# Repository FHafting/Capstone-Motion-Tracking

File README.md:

# Capstone Motion Tracking
 Repository for MSE4499 capstone project

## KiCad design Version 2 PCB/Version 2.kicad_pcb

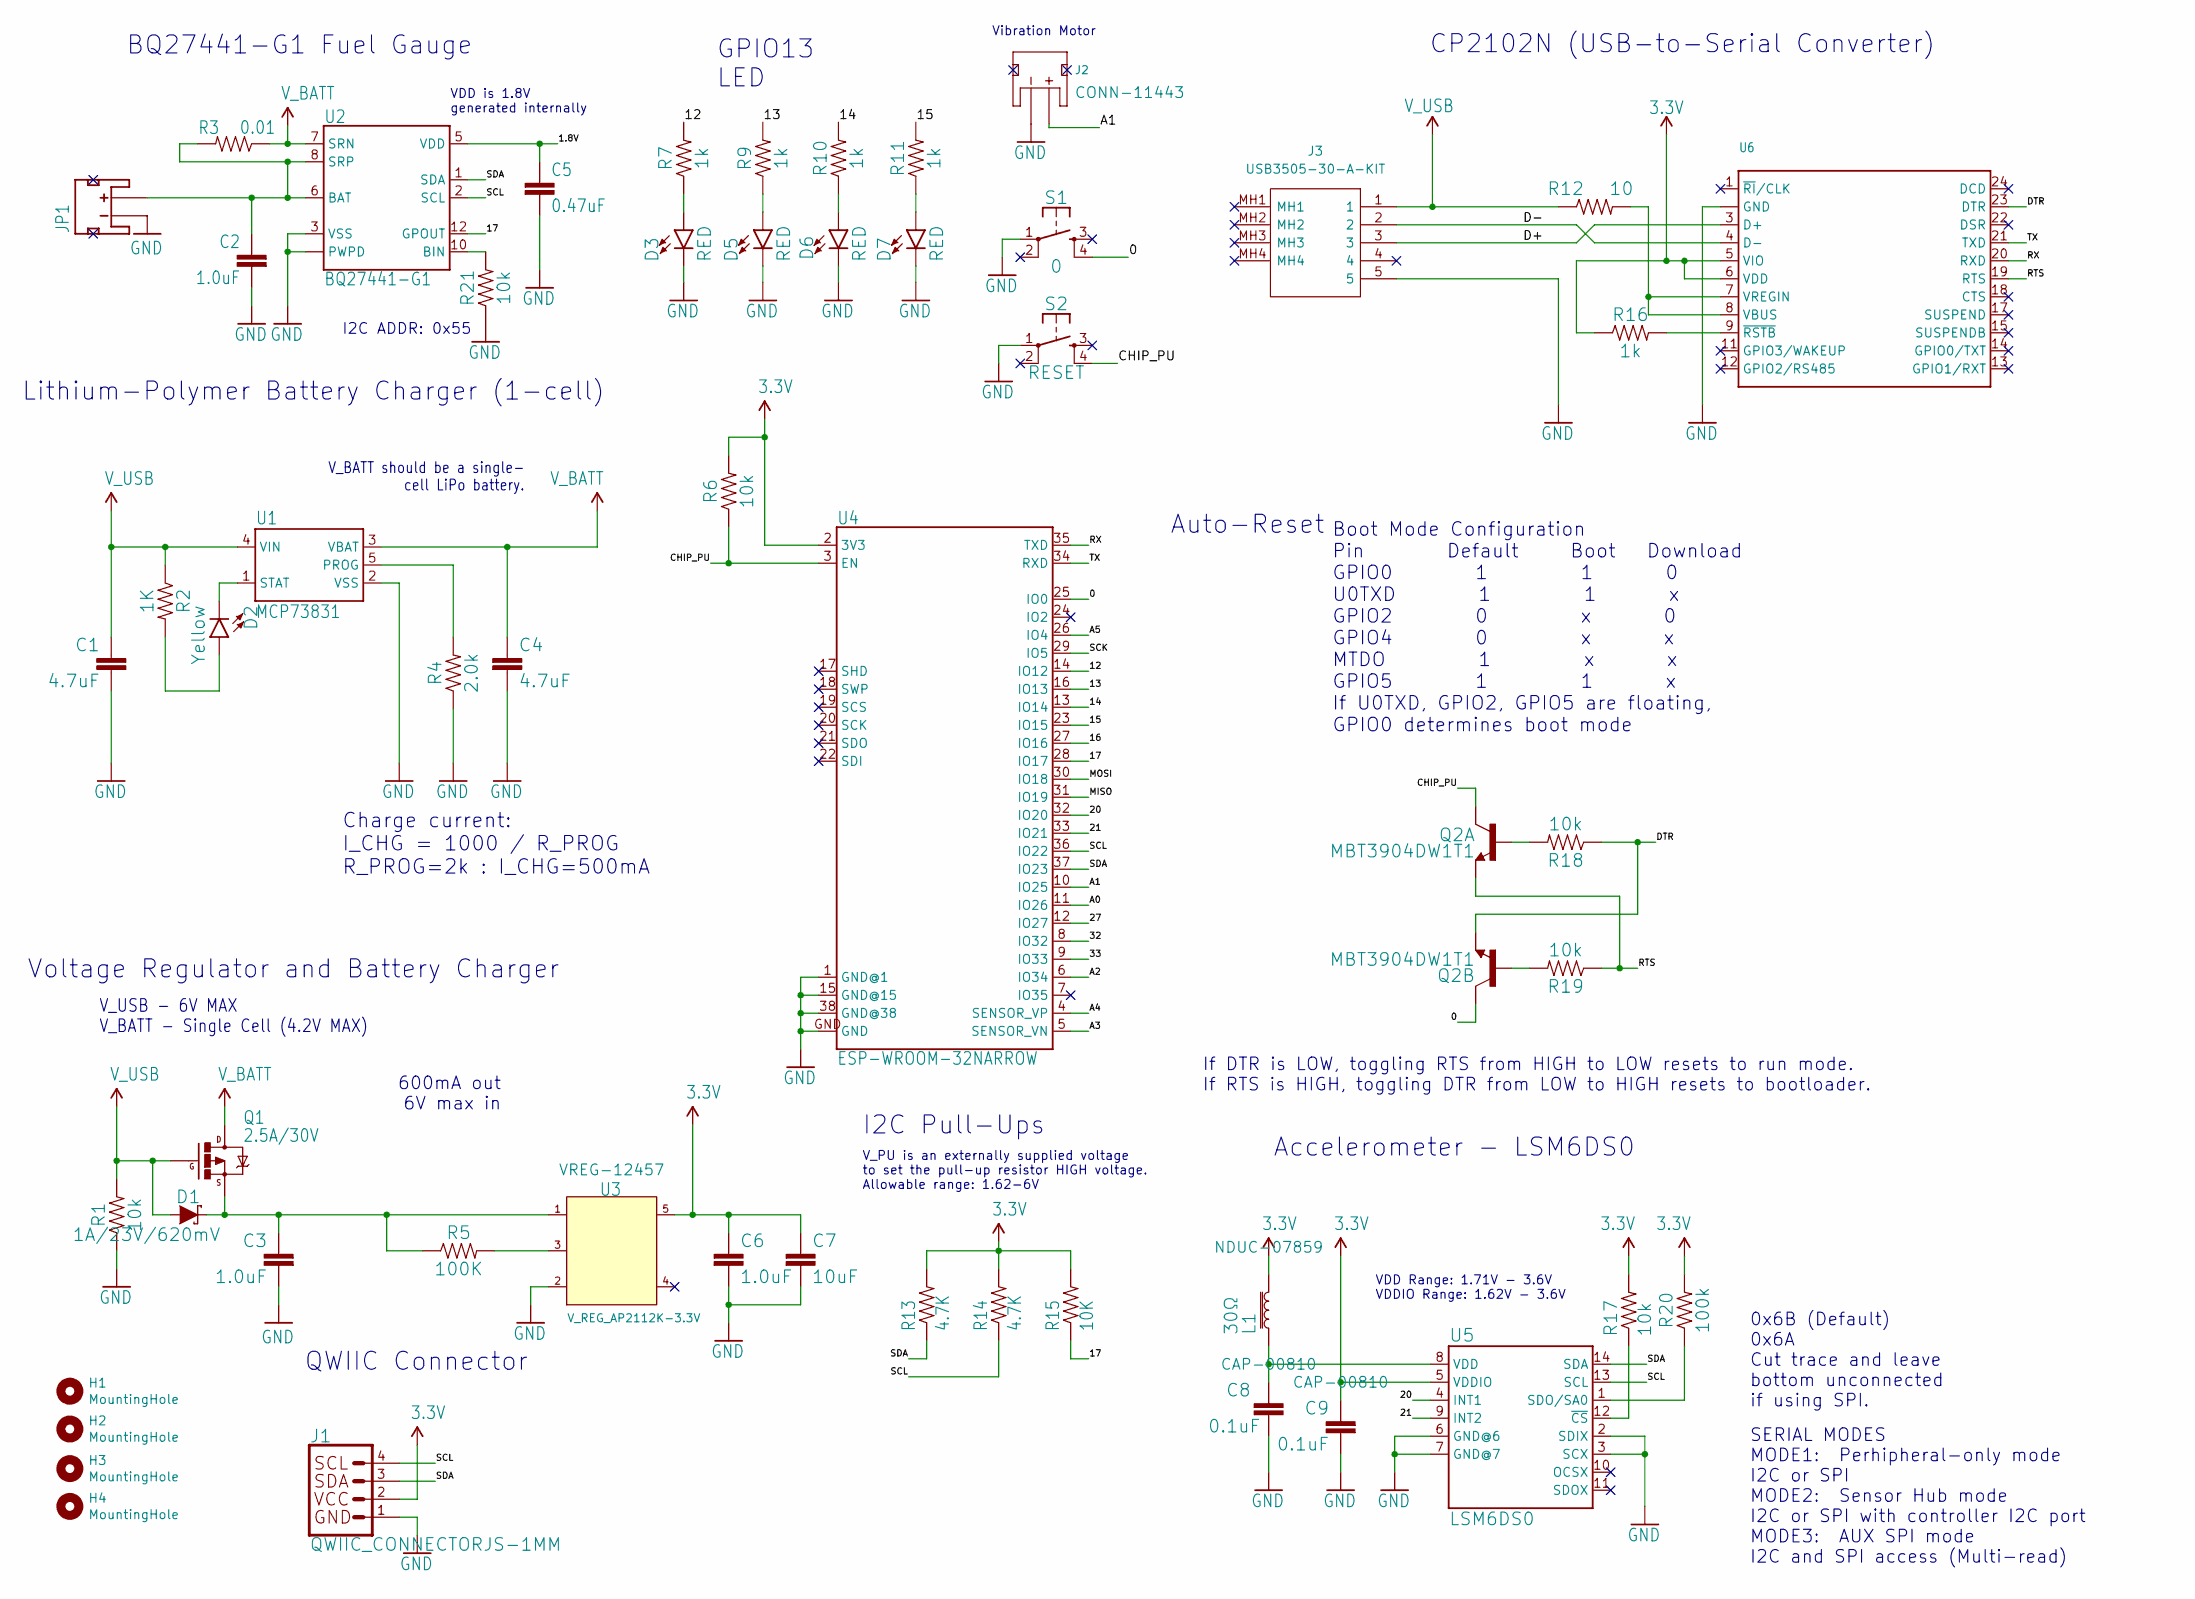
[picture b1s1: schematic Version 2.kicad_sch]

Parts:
C1, C4: 4.7uF; C_0603_1608Metric
C2, C3: 1.0uF; C_0603_1608Metric
C5: C_0603_1608Metric
C6: 1.0uF; 0402
C7: 10uF; C_0603_1608Metric
C8, C9: 0.1uF; C_0603_1608Metric
D1: 1A/23V/620mV; D_SOD-323
D2: Yellow; LED-0603
D3, D5, D6, D7: RED; LED-0603
H1, H2, H3, H4: MountingHole; MountingHole_2mm
J1: QWIIC_CONNECTORJS-1MM; 1X04_1MM_RA
J2: JST_2MM_MALE; JST-2-SMD
J3: USB3505-30-A-KIT; USB350530AKIT; Manufacturer_Part_Number USB3505-30-A-KIT; Mouser Part Number 640-USB3505-30-A-KIT
JP1: JST_2MM_MALE; JST-2-SMD
L1: 30Ω; 0603
Q1: 2.5A/30V; SOT23-3
Q2: MBT3904DW1T1; SC70-6
R1, R6, R17, R18, R19, R21: 10k; 0603
R2: 1K; 0603
R3: 1206
R4: 2.0k; 0603
R5: 100K; 0402
R7, R9, R10, R11, R16: 1k; 0603
R12: 10; 0603
R13, R14: 4.7K; 0603
R15: 10K; 0603
R20: 100k; 0603
S1: 0; TACTILE_SWITCH_SMD_4.6X2.8MM
S2: RESET; TACTILE_SWITCH_SMD_4.6X2.8MM
U1: MCP73831; SOT23-5
U2: PDSO-N12
U3: V_REG_AP2112K-3.3V; SOT23-5
U4: ESP32-WROOM-32
U5: LSM6DS0; LGA-14_3x2.5mm_P0.5mm_LayoutBorder3x4y
U6: (no value)

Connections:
3.3V: C6.1, C7.1, C9.1, J1.2, L1.1, R6.2, R13.2, R14.2, R15.2, R16.1, R17.2, R20.2, U3.5 (OUT), U4.2 (3V3), U5.5 (VDDIO), U6.5 (VIO), U6.6 (VDD)
/0: Q2.6 (C), S1.4, U4.25 (IO0)
/1.8V: C5.1, U2.5 (VDD)
/12: R7.2, U4.14 (IO12)
/13: R9.2, U4.16 (IO13)
/14: R10.2, U4.13 (IO14)
/15: R11.2, U4.23 (IO15)
/16: U4.27 (IO16)
/17: R15.1, U2.12 (GPOUT), U4.28 (IO17)
/20: U4.32 (IO20), U5.4 (INT1)
/21: U4.33 (IO21), U5.9 (INT2)
/27: U4.12 (IO27)
/32: U4.8 (IO32)
/33: U4.9 (IO33)
/A0: U4.11 (IO26)
/A1: J2.2 (+), U4.10 (IO25)
/A2: U4.6 (IO34)
/A3: U4.5 (SENSOR_VN)
/A4: U4.4 (SENSOR_VP)
/A5: U4.26 (IO4)
/CHIP_PU: Q2.3 (C), R6.1, S2.4, U4.3 (EN)
/D+: J3.3, U6.3 (D+)
/D-: J3.2, U6.4 (D-)
/DTR: Q2.1 (E), R18.1, U6.23 (DTR)
/MISO: U4.31 (IO19)
/MOSI: U4.30 (IO18)
/RTS: Q2.4 (E), R19.1, U6.19 (RTS)
/RX: U4.35 (TXD), U6.20 (RXD)
/SCK: U4.29 (IO5)
/SCL: J1.4, R14.1, U2.2 (SCL), U4.36 (IO22), U5.13 (SCL)
/SDA: J1.3, R13.1, U2.1 (SDA), U4.37 (IO23), U5.14 (SDA)
/TX: U4.34 (RXD), U6.21 (TXD)
GND: C1.2, C2.2, C3.2, C4.2, C5.2, C6.2, C7.2, C8.2, C9.2, D3.C, D5.C, D6.C, D7.C, J1.1, J2.1 (-), J3.5, JP1.1 (-), R1.1, R4.1, R21.1, S1.1, S2.1, U1.2 (VSS), U2.3 (VSS), U2.EP (PWPD), U2.EP1 (PWPD), U2.EP2 (PWPD), U2.EP3 (PWPD), U2.EP4 (PWPD), U3.2 (GND), U4.1 (GND@1), U4.15 (GND@15), U4.38 (GND@38), U4.GND, U5.2 (SDIX), U5.3 (SCX), U5.6 (GND@6), U5.7 (GND@7), U6.2 (GND), U6.PAD (GND)
unnamed: C2.1, JP1.2 (+), R3.2, U2.6 (BAT), U2.8 (SRP)
unnamed: C3.1, D1.1 (C), Q1.2 (S), R5.1, U3.1 (IN)
unnamed: C8.1, L1.2, U5.8 (VDD)
unnamed: D2.A, R2.2
unnamed: D2.C, U1.1 (STAT)
unnamed: D3.A, R7.1
unnamed: D5.A, R9.1
unnamed: D6.A, R10.1
unnamed: D7.A, R11.1
unnamed: Q2.2 (B), R19.2
unnamed: Q2.5 (B), R18.2
unnamed: R4.2, U1.5 (PROG)
unnamed: R5.2, U3.3 (EN)
unnamed: R12.2, U6.7 (VREGIN), U6.8 (VBUS)
unnamed: R16.2, U6.9 (~RSTB)
unnamed: R17.1, U5.12 (~CS)
unnamed: R20.1, U5.1 (SDO/SA0)
unnamed: R21.2, U2.10 (BIN)
V_BATT: C4.1, Q1.3 (D), R3.1, U1.3 (VBAT), U2.7 (SRN)
V_USB: C1.1, D1.2 (A), J3.1, Q1.1 (G), R1.2, R2.1, R12.1, U1.4 (VIN)

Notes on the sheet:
GPIO13 LED
I2C ADDR: 0x55
VDD Range: 1.71V - 3.6V VDDIO Range: 1.62V - 3.6V
V_PU is an externally supplied voltage to set the pull-up resistor HIGH voltage. Allowable range: 1.62-6V
VDD is 1.8V generated internally
SERIAL MODES MODE1: Perhipheral-only mode I2C or SPI MODE2: Sensor Hub mode I2C or SPI with controller I2C port MODE3: AUX SPI mode I2C and SPI access (Multi-read)
Boot Mode Configuration Pin Default Boot Download GPIO0 1 1 0 U0TXD 1 1 x GPIO2 0 x 0 GPIO4 0 x x MTDO 1 x x GPIO5 1 1 x If U0TXD, GPIO2, GPIO5 are floating, GPIO0 determines boot mode
Auto-Reset
Vibration Motor
QWIIC Connector
I2C Pull-Ups
600mA out 6V max in
CP2102N (USB-to-Serial Converter)
Charge current: I_CHG = 1000 / R_PROG R_PROG=2k : I_CHG=500mA
V_USB - 6V MAX V_BATT - Single Cell (4.2V MAX)
If DTR is LOW, toggling RTS from HIGH to LOW resets to run mode. If RTS is HIGH, toggling DTR from LOW to HIGH resets to bootloader.
BQ27441-G1 Fuel Gauge
Lithium-Polymer Battery Charger (1-cell)
Accelerometer - LSM6DS0
V_BATT should be a single- cell LiPo battery.
Voltage Regulator and Battery Charger
0x6B (Default) 0x6A Cut trace and leave bottom unconnected if using SPI.

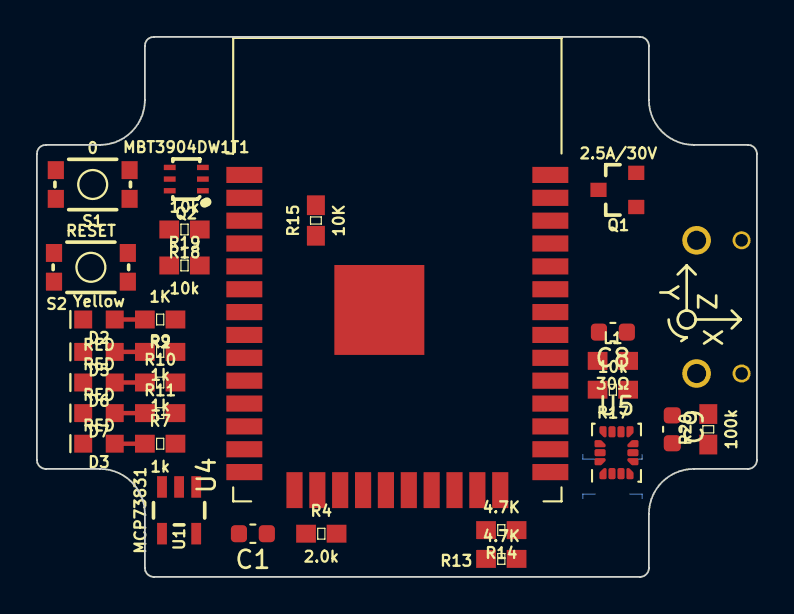
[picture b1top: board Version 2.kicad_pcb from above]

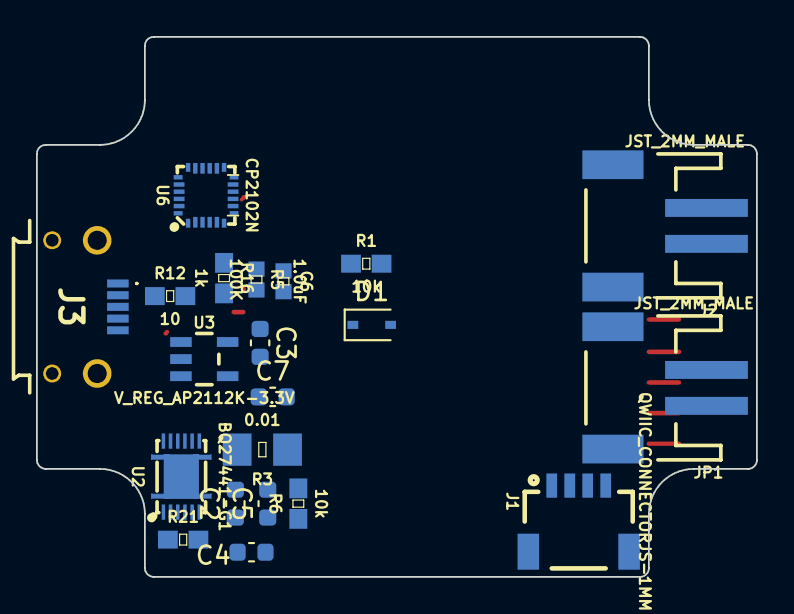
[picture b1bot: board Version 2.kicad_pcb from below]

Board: 2 copper layers, 40.0 x 30.0 mm, 50 parts (21 on the bottom side), 41 nets.

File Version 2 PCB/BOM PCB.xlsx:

References | Value | Footprint | Quantity | Price | URL
C1, C4 | 4.7uF | C_0603_1608Metric | 2 | 0.74 | https://www.digikey.ca/en/products/detail/kyocera-avx/CM105X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
C2, C3 | 1.0uF | C_0603_1608Metric | 2 | 0.28000000000000003 | https://www.digikey.ca/en/products/detail/samsung-electro-me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
C8, C9 | 0.1uF | C_0603_1608Metric | 2 | 0.28000000000000003 | https://www.digikey.ca/en/products/detail/walsin-technology-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
C5 | 0.47uF | C_0603_1608Metric | 1 | 0.14000000000000001 | https://www.digikey.ca/en/products/detail/w%C3%BCrth-elektro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
C6 | 1.0uF | 402 | 1 | 0.14000000000000001 | https://www.digikey.ca/en/products/detail/walsin-technology-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
C7 | 10uF | C_0603_1608Metric | 1 | 0.36 | https://www.digikey.ca/en/products/detail/murata-electronics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
R2, R7, R8, R9, R10, R11, R16 | 1k | 603 | 7 | 3.57 | https://www.digikey.ca/en/products/detail/vishay-beyschlag-d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
R1, R6, R15, R17, R18, R19 | 10k | 603 | 6 | 3.06 | https://www.digikey.ca/en/products/detail/vishay-beyschlag-d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
R13, R14 | 4.7K | 603 | 2 | 1.22 | https://www.digikey.ca/en/products/detail/vishay-beyschlag-d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
R3 | 0.01 | 1206 | 1 | 0.95 | https://www.digikey.ca/en/products/detail/bourns-inc/CRF1206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
R4 | 2.0k | 603 | 1 | 0.74 | https://www.digikey.ca/en/products/detail/vishay-beyschlag-d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
R5 | 100K | 402 | 1 | 0.18 | https://www.digikey.ca/en/products/detail/stackpole-electron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
R12 | 10 | 603 | 1 | 0.49 | https://www.digikey.ca/en/products/detail/panasonic-electron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
R20 | 100k | 603 | 1 | 0.51 | https://www.digikey.ca/en/products/detail/vishay-beyschlag-d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
L1 | 30 ohm | 603 | 1 | 0.3 | https://www.digikey.ca/en/products/detail/tdk-corporation/NT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
D3, D4, D5, D6, D7 | RED | LED_0603_1608Metric | 5 | 2.2000000000000002 | https://www.digikey.ca/en/products/detail/osram-opto-ams-osr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
D1 | 1A/23V/620mV | D_SOD-323 | 1 | 0.57999999999999996 | https://www.digikey.ca/en/products/detail/stmicroelectronics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
D2 | Yellow | LED_0603_1608Metric | 1 | 0.6 | https://www.digikey.ca/en/products/detail/dialight/599004000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
U1 | MCP73831 | SOT23-5 | 1 | 1.17 | https://www.digikey.ca/en/products/detail/microchip-technolo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
U2 | BQ27441-G1 | PDSO-N12 | 1 | 2.83 | https://www.digikey.ca/en/products/detail/texas-instruments/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
U3 | AP2112K-3.3V | SOT23-5 | 1 | 0.56999999999999995 | https://www.digikey.ca/en/products/detail/diodes-incorporate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
U4 | ESP-WROOM-32NARROW | ESP32-WROOM-32 | 1 | 4.5999999999999996 | https://www.digikey.ca/en/products/detail/espressif-systems/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
U5 | LSM6DSO | LGA-14_3x2.5mm_P0.5mm_LayoutBorder3x4y | 1 | 6.6 | https://www.digikey.ca/en/products/detail/stmicroelectronics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
U6 | CP2102N | QFN24-3X3 | 1 | 6.4 | https://www.digikey.ca/en/products/detail/silicon-labs/CP210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
Q1 | 2.5A/30V | SOT23-3 | 1 | 0.76 | https://www.digikey.ca/en/products/detail/vishay-siliconix/S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
Q2 | MBT3904DW1T1 | SC70-6 | 1 | 0.4 | https://www.digikey.ca/en/products/detail/onsemi/MBT3904DW1T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
S1 | 0 | TACTILE_SWITCH_SMD_4.6X2.8MM | 1 | 0.68 | https://www.digikey.ca/en/products/detail/c-k/KMR221NG-LFS/2176483
S2 | RESET | TACTILE_SWITCH_SMD_4.6X2.8MM | 1 | 0.68 | https://www.digikey.ca/en/products/detail/c-k/KMR221NG-LFS/2176483
J2, JP1 | JST_2MM_MALE | JST-2-SMD | 2 | 0.56999999999999995 | https://www.digikey.ca/en/products/detail/jst-sales-america-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
J1 | QWIIC_CONNECTORJS-1MM | 1X04_1MM_RA | 1 | 0.54500000000000004 | https://www.mouser.ca/ProductDetail/Adafruit/4208?qs=PzGy0jf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
J3 | USB_MICRO-B_HALF_PTH_MILL | USB-MICROB-PTH | 1 | 3.44 | https://www.mouser.ca/ProductDetail/GCT/USB3505-30-A?qs=iLbe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
 | Vibration Motor |  | 1 | 1.84 | https://www.digikey.ca/en/products/detail/seeed-technology-c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
 |  |  | Total | 47.424999999999997

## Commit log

2022-11-15 Wifi STA working with single MPU sensor
2022-11-23 Adding 10msTimer, Sample ESP32 RX and TX Code
2022-11-23 stored time in a variable
2022-11-24 Added Charts and get functions for Accel y, z
2022-11-24 readme update
2022-11-24 updating Readme
2022-11-24 renamed: ESP32TX and ESP32RXTX
2022-11-24 follow-up to the rename
2023-02-12 Added functionality to manually switch wifi modes
2023-02-24 added esp now functionality (still missing json string construction)
2023-02-24 changed folder name
2023-02-24 replicated data structure in sender as reciever
2023-02-24 esp now - verified for non-array data
2023-02-24 code works for time and id values at 100 ms
2023-02-25 verified performance of esp now
2023-02-25 pending: convert received data to json
2023-02-25 constructed preliminary json code but has glitches
2023-02-25 working JSON code with no errors
2023-02-25 max packet size - 9 - esp now sending data at 11hz
2023-02-25 LED 2 toggles when sender sends data
2023-02-25 esp status boolean causing some issues in json
2023-02-25 trying to resolve issue with status boolean
2023-02-25 syntax error
2023-03-03 Update sender.io with real IMU data from Sparkfun LSM6DS3 library
2023-03-03 syntax updates to receiver
2023-03-03 added sparkfun library
2023-03-03 added sparkfun library again!
2023-03-03 Added PCB files
2023-03-03 Added BOM and CAD files of PCB
2023-03-03 Created new libraries folder
2023-03-03 Added testing codes
2023-03-03 Adding Android App!
2023-03-03 Refined Code
2023-03-03 Adding CapstoneApp
2023-03-22 sender and receiver code for debugging
2023-03-23 relocating app
2023-03-23 Creating a new app
2023-03-23 Completed set up for mainActivity.java and created DeviceOptionsActivity.java.
2023-03-23 Added network_security_config.xml
2023-03-23 Added url exeception and relocated network_security_config.xml to the correct folder
2023-03-24 Added timer and status functionality - now if device is not connected, app can tell the user something is wrong
2023-03-24 adding device detection (not complete), with flags everywhere
2023-03-24 separated low priority tasks from json parsing and fixed active devices (somewhat)
2023-03-27 added database - it works fine in simulator but is causing issues in the android device
2023-03-27 got some database working - most primitive format - must modify methods now to account for data coming from various boards
2023-03-27 working database within deviceOptionsActivity.java, but needs to be implemented to store the sensor data
    Also database enabled for single board only
2023-03-29 changed packet size and amount of boards to 10
2023-03-30 added datarate
2023-03-30 added datarate, disabled database
2023-03-31 reorganized functions, fixed /values
2023-04-01 added ping test and organized the code
2023-04-01 added timer reset - receiver sending reset signals
2023-04-01 rearranged code
2023-04-01 removed database - will try to implement sharedpreferences after reducing the variables storing sensor data
2023-04-03 in the process of implementing csv file, spinner and chart but exploring new ways to implement csv (changing code after this save)
2023-04-04 added full chart functionality but i think this method is creating too many handler requests so other methods will be explored
2023-04-05 debugging issues with packet losses
2023-04-05 tested code for all three programs
2023-04-05 working code!
2023-04-09 updated files
